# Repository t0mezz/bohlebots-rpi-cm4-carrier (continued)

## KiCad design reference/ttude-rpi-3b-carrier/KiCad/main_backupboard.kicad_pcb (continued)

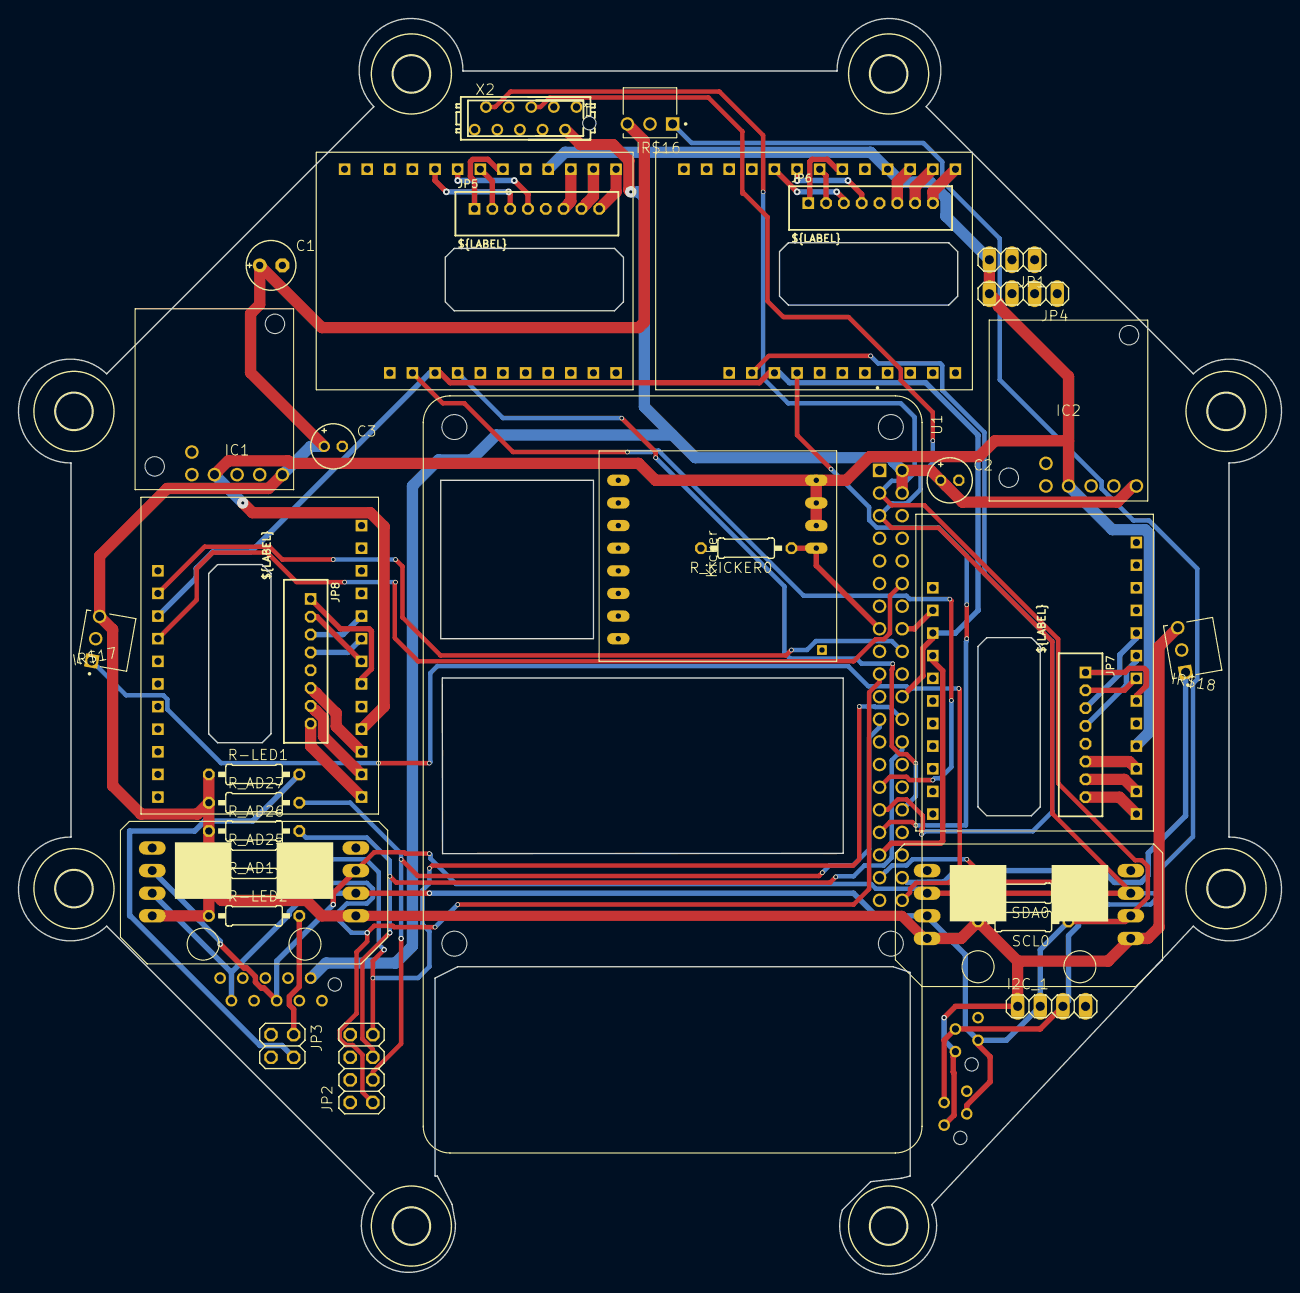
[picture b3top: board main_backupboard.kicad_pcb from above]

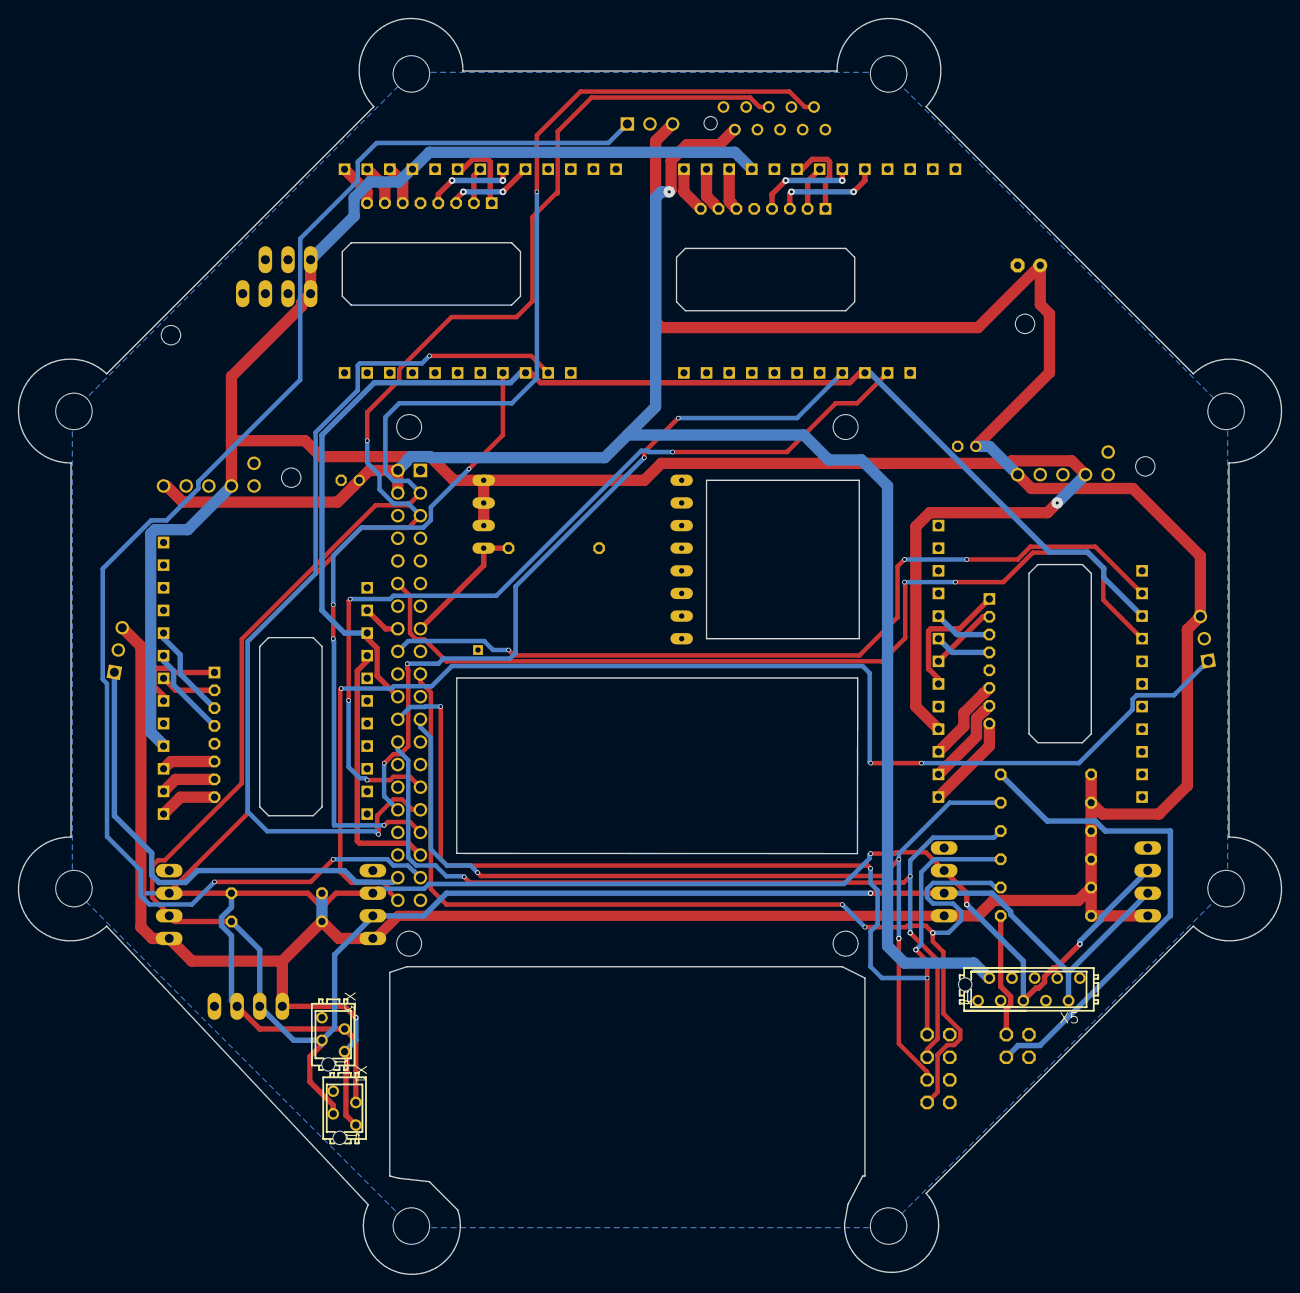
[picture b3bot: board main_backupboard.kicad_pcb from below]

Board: 2 copper layers, 141.8 x 141.0 mm, 46 parts (3 on the bottom side), 54 nets.

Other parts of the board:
U$5, U$6, U$7, U$10, U$11, U$12, U$13, U$14: 4,1

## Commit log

2023-12-05 Schaltplan Update
2023-12-05 Test change
2023-12-05 Schematic Update
2023-12-06 Random changes.
2023-12-06 Added USB and i2c connector for groundsensor.
2023-12-06 Added Motordrivers.
2023-12-06 Save.
2023-12-07 Added step downs.
2023-12-07 Added I2C pullup
2023-12-08 Some small changes, probably first finished schematic.
2023-12-10 Finished Schematic, started pcb.
2023-12-10 Some configuartions for pcb.
2023-12-11 Added esd protection TODO: find fitting tvs diode (tht) 2p, 4p
2023-12-13 Added tsv diodes.
2023-12-13 Started routing.
2023-12-13 PCB Layout Update.
2023-12-21 Updated pcb layout.
2023-12-27 IC placement done.
2023-12-29 V01 finished.
2024-01-01 V01.2 Update.
2024-01-18 Added dxf files.
2024-01-18 Renames.
2024-01-18 Renames again.
2024-01-19 Added some vias.
2024-01-19 Added some file system changes.
2024-01-19 test
2024-01-19 test2
2024-01-19 Added qr-c, fixed 'single connector footpring' issue, added compensation vias.
2024-01-19 Updated render img.
2024-01-21 v2.0 finished.
